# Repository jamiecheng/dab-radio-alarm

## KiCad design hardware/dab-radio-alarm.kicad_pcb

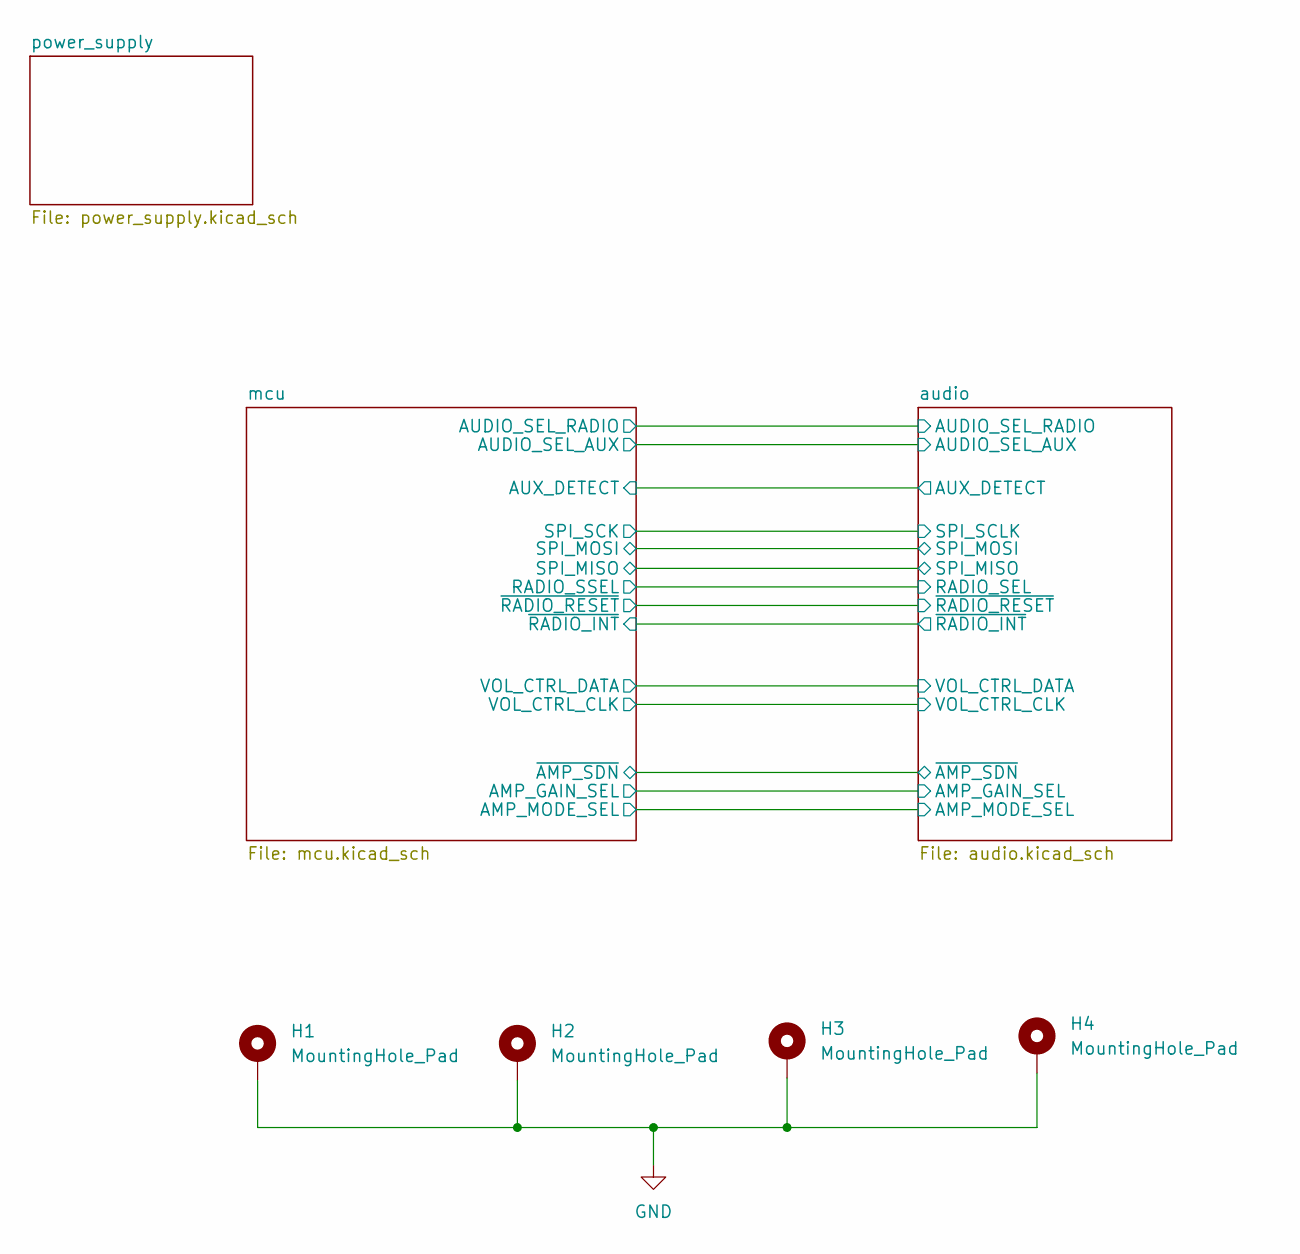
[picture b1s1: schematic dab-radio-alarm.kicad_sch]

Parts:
H1, H2, H3, H4: MountingHole_Pad; MountingHole_3.2mm_M3_Pad_Via

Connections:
GND: H1.1, H2.1, H3.1, H4.1; also elsewhere on the board

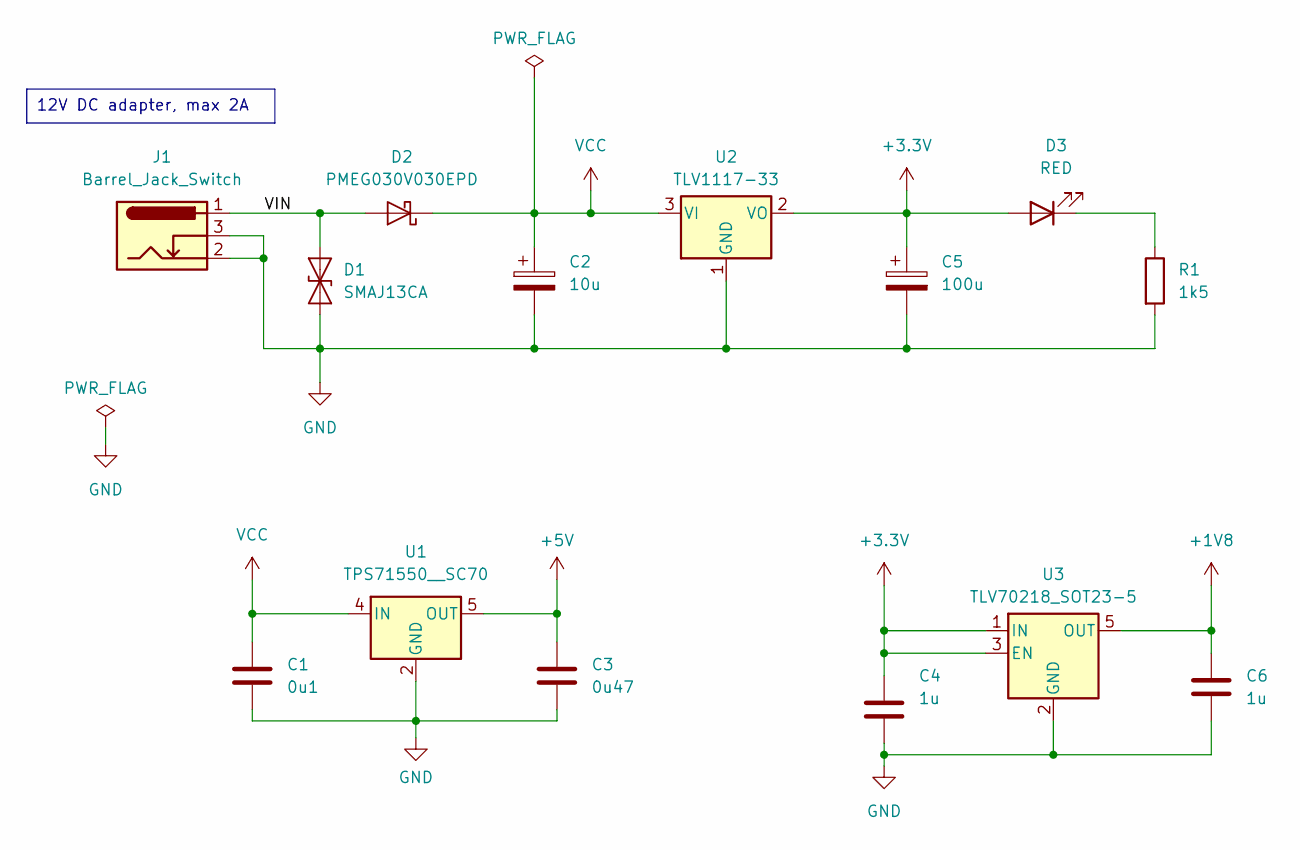
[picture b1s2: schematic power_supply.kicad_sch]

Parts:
C1: 0u1; C_0603_1608Metric
C2: 10u; CP_Elec_6.3x5.4
C3: 0u47; C_0402_1005Metric
C4, C6: 1u; C_0402_1005Metric
C5: 100u; CP_Elec_8x10
D1: SMAJ13CA; D_SMA
D2: PMEG030V030EPD; Nexperia_CFP15_SOT-1289
D3: RED; LED_0603_1608Metric
J1: Barrel_Jack_Switch; BarrelJack_GCT_DCJ200-10-A_Horizontal
R1: 1k5; R_0402_1005Metric
U1: TPS71550__SC70; SOT-353_SC-70-5
U2: TLV1117-33; SOT-223-3_TabPin2
U3: TLV70218_SOT23-5; SOT-23-5

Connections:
+1V8: C6.1, U3.5 (OUT); also elsewhere on the board
+3.3V: C4.1, C5.1, D3.2 (A), U2.2 (VO), U3.1 (IN), U3.3 (EN); also elsewhere on the board
+5V: C3.1, U1.5 (OUT); also elsewhere on the board
/power_supply/VIN: D1.1 (A1), D2.1 (A), D2.2 (A), J1.1
GND: C1.2, C2.2, C3.2, C4.2, C5.2, C6.2, D1.2 (A2), J1.2, J1.3, R1.2, U1.2 (GND), U2.1 (GND), U3.2 (GND); also elsewhere on the board
unnamed: D3.1 (K), R1.1
VCC: C1.1, C2.1, D2.3 (K), U1.4 (IN), U2.3 (VI); also elsewhere on the board

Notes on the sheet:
12V DC adapter, max 2A

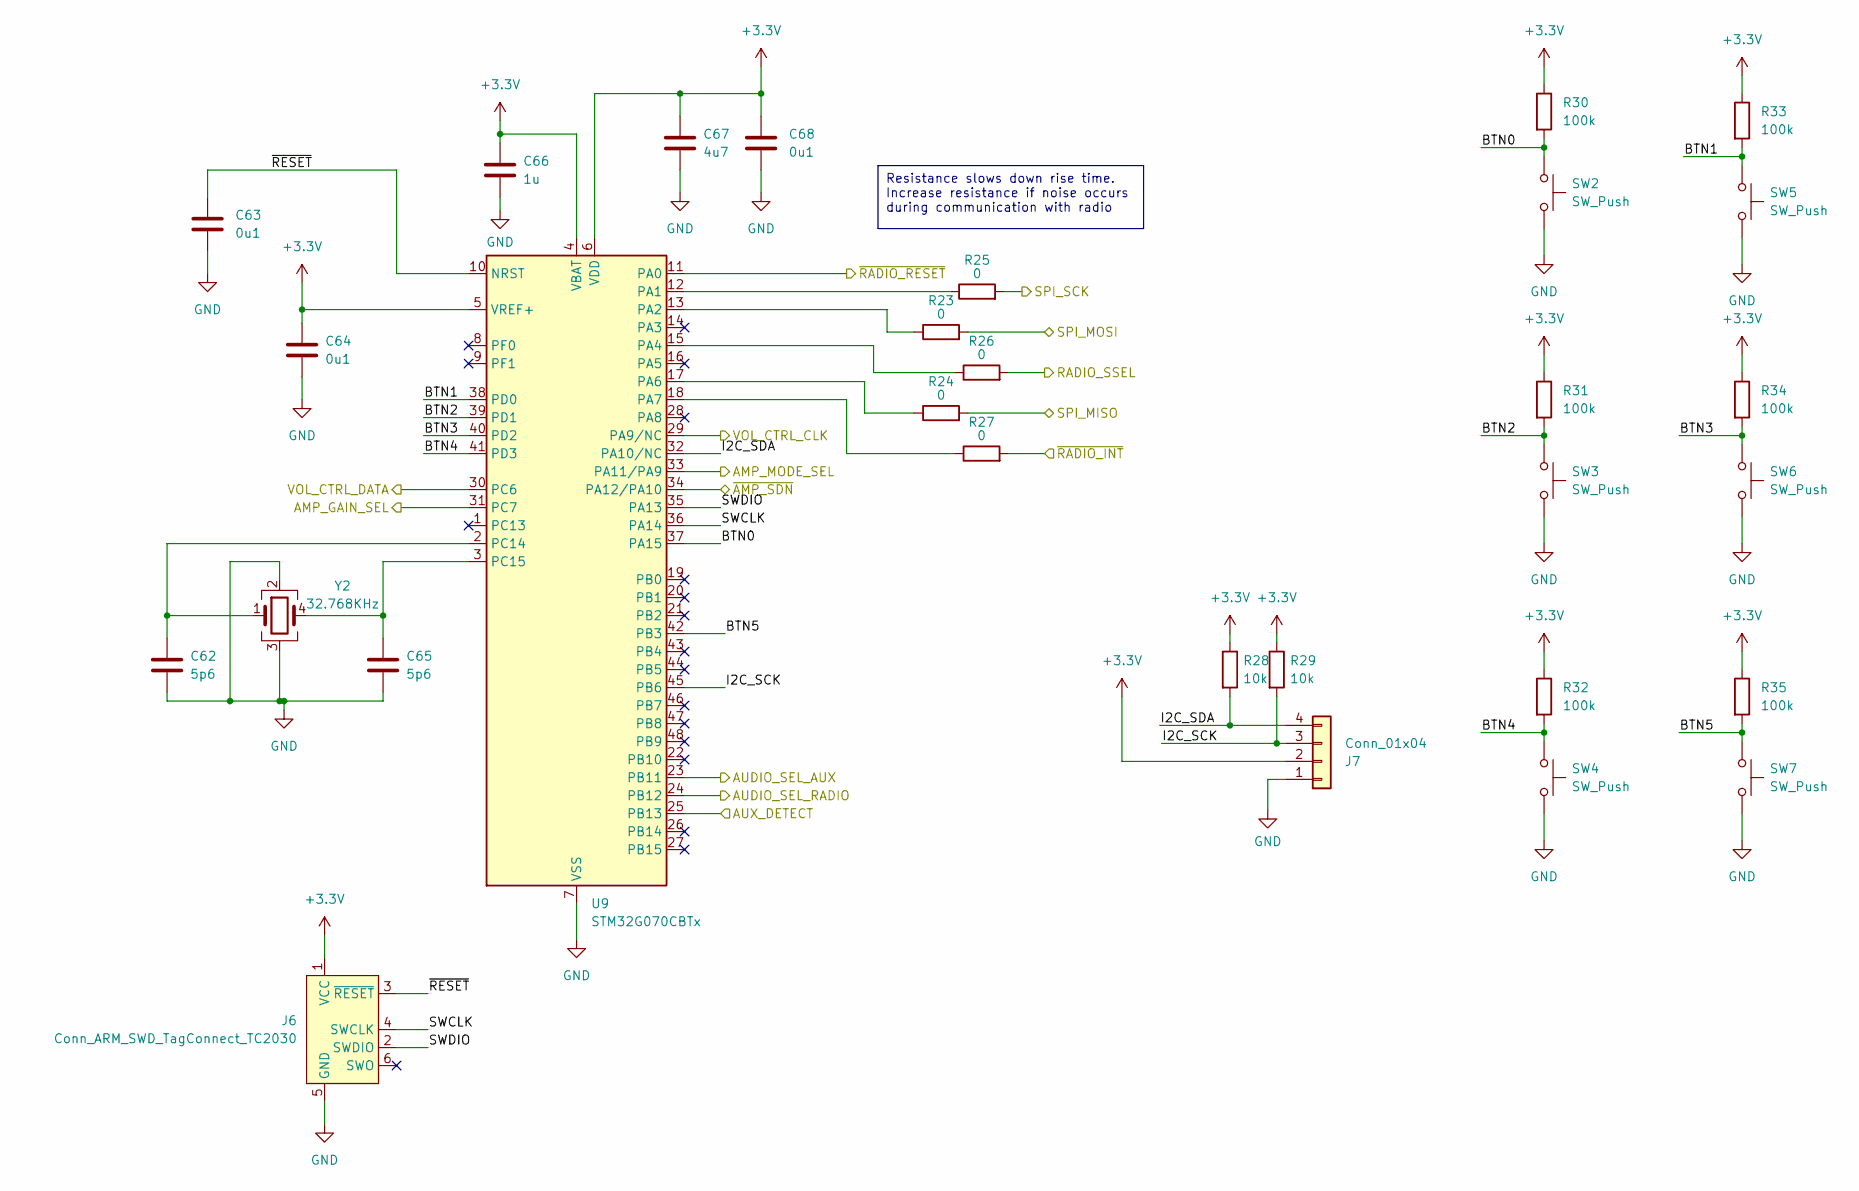
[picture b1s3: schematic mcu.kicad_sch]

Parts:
C62, C65: 5p6; C_0402_1005Metric
C63, C64, C68: 0u1; C_0402_1005Metric
C66: 1u; C_0402_1005Metric
C67: 4u7; C_0603_1608Metric
J6: Conn_ARM_SWD_TagConnect_TC2030; Tag-Connect_TC2030-IDC-FP_2x03_P1.27mm_Vertical
J7: Conn_01x04; PinHeader_1x04_P2.54mm_Vertical
R23, R24, R25, R26, R27: 0; R_0402_1005Metric
R28, R29: 10k; R_0402_1005Metric
R30, R31, R32, R33, R34, R35: 100k; R_0402_1005Metric
SW2, SW3, SW4, SW5, SW6, SW7: SW_Push; SW_PUSH_6mm_H5mm
U9: STM32G070CBTx; LQFP-48_7x7mm_P0.5mm
Y2: 32.768KHz; Crystal_SMD_3225-4Pin_3.2x2.5mm

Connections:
+3.3V: C64.1, C66.1, C67.1, C68.1, J6.1 (VCC), J7.2, R28.1, R29.1, R30.1, R31.1, R32.1, R33.1, R34.1, R35.1, U9.4 (VBAT), U9.5 (VREF+), U9.6 (VDD); also elsewhere on the board
/audio/AMP_GAIN_SEL: U9.31 (PC7); also elsewhere on the board
/audio/AMP_MODE_SEL: U9.33 (PA11/PA9); also elsewhere on the board
/audio/AUDIO_SEL_AUX: U9.23 (PB11); also elsewhere on the board
/audio/AUDIO_SEL_RADIO: U9.24 (PB12); also elsewhere on the board
/audio/AUX_DETECT: U9.25 (PB13); also elsewhere on the board
/audio/RADIO_SEL: R26.2; also elsewhere on the board
/audio/SPI_MISO: R24.2; also elsewhere on the board
/audio/SPI_MOSI: R23.2; also elsewhere on the board
/audio/SPI_SCLK: R25.2; also elsewhere on the board
/audio/VOL_CTRL_CLK: U9.29 (PA9/NC); also elsewhere on the board
/audio/VOL_CTRL_DATA: U9.30 (PC6); also elsewhere on the board
/audio/~AMP_SDN: U9.34 (PA12/PA10); also elsewhere on the board
/audio/~RADIO_INT: R27.2; also elsewhere on the board
/audio/~RADIO_RESET: U9.11 (PA0); also elsewhere on the board
/mcu/BTN0: R30.2, SW2.1, U9.37 (PA15)
/mcu/BTN1: R33.2, SW5.1, U9.38 (PD0)
/mcu/BTN2: R31.2, SW3.1, U9.39 (PD1)
/mcu/BTN3: R34.2, SW6.1, U9.40 (PD2)
/mcu/BTN4: R32.2, SW4.1, U9.41 (PD3)
/mcu/BTN5: R35.2, SW7.1, U9.42 (PB3)
/mcu/I2C_SCK: J7.3, R29.2, U9.45 (PB6)
/mcu/I2C_SDA: J7.4, R28.2, U9.32 (PA10/NC)
/mcu/SWCLK: J6.4 (SWCLK), U9.36 (PA14)
/mcu/SWDIO: J6.2 (SWDIO), U9.35 (PA13)
/mcu/~RESET: C63.1, J6.3 (~RESET), U9.10 (NRST)
GND: C62.2, C63.2, C64.2, C65.2, C66.2, C67.2, C68.2, J6.5 (GND), J7.1, SW2.2, SW3.2, SW4.2, SW5.2, SW6.2, SW7.2, U9.7 (VSS), Y2.2, Y2.3; also elsewhere on the board
unnamed: R25.1, U9.12 (PA1)
unnamed: R23.1, U9.13 (PA2)
unnamed: R26.1, U9.15 (PA4)
unnamed: R24.1, U9.17 (PA6)
unnamed: R27.1, U9.18 (PA7)
unnamed: C62.1, U9.2 (PC14), Y2.1
unnamed: C65.1, U9.3 (PC15), Y2.4

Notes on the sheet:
Resistance slows down rise time. Increase resistance if noise occurs during communication with radio

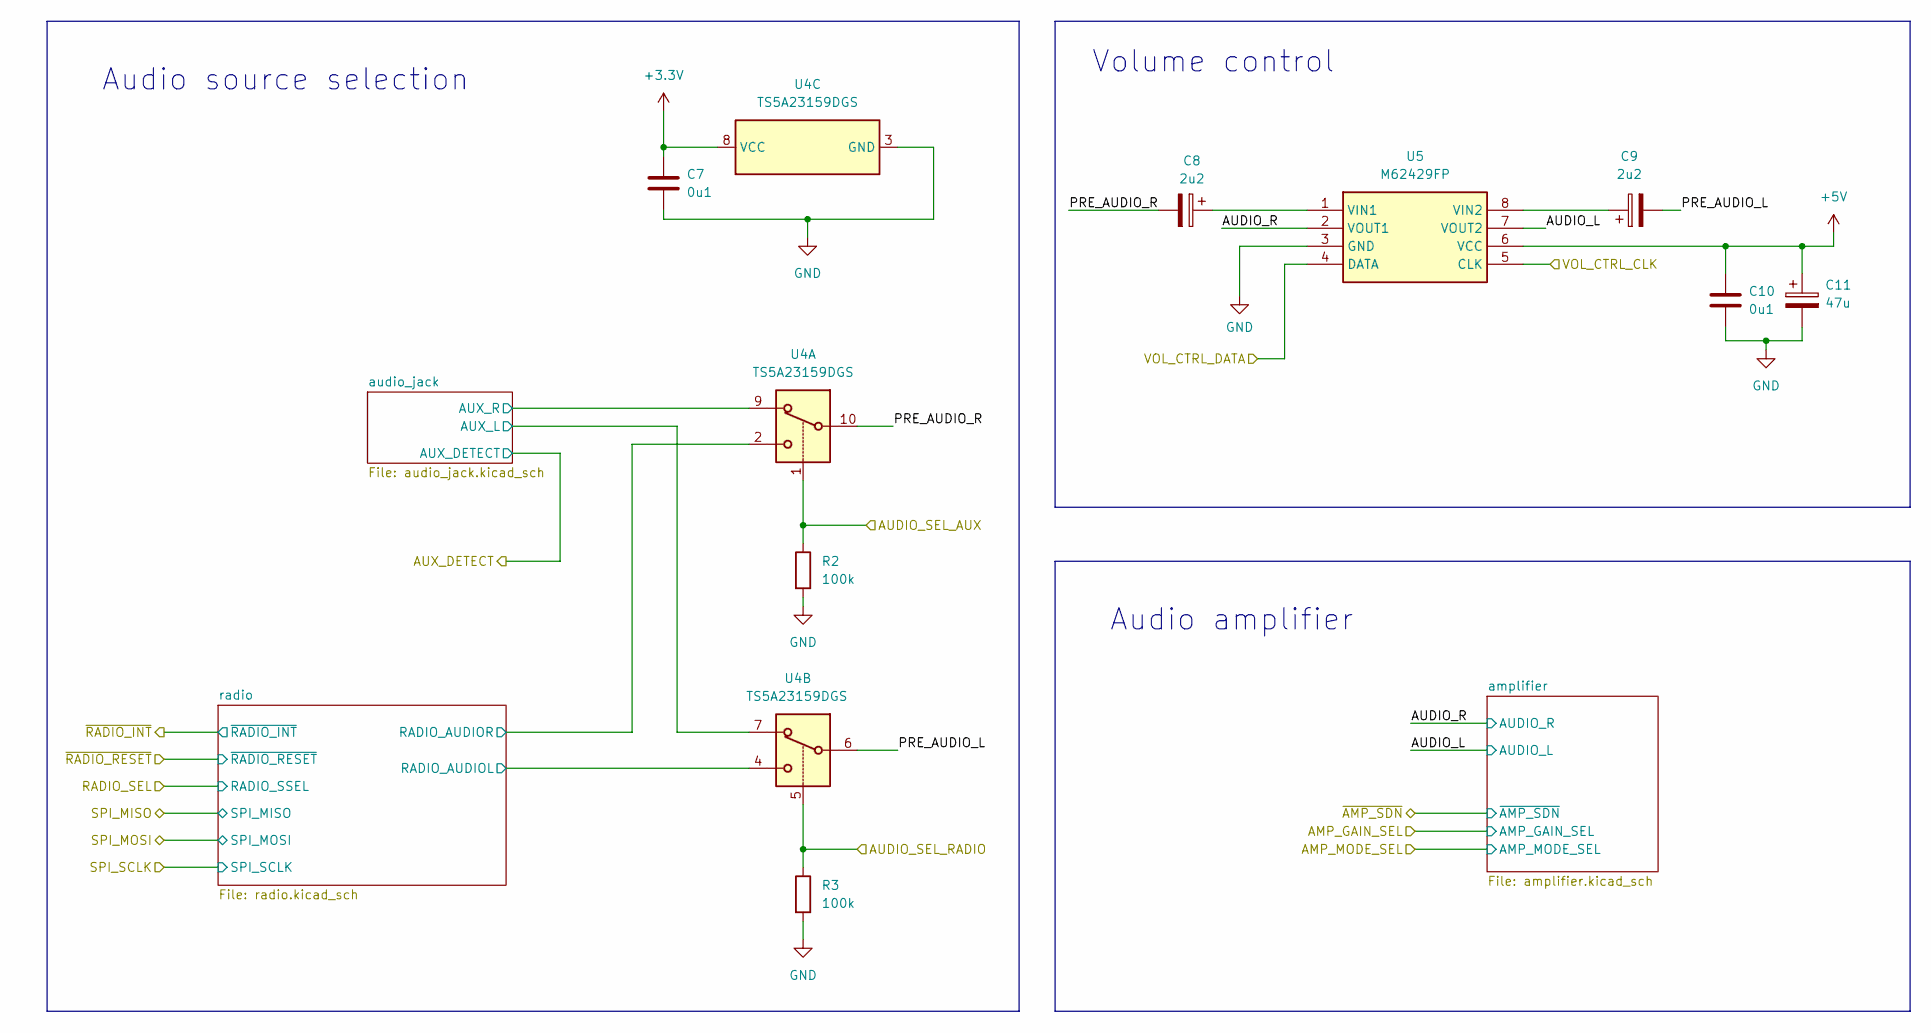
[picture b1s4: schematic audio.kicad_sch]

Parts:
C7, C10: 0u1; C_0402_1005Metric
C8, C9: 2u2; CP_Elec_4x5.4
C11: 47u; CP_Elec_5x5.4
R2, R3: 100k; R_0402_1005Metric
U4: TS5A23159DGS; VSSOP-10_3x3mm_P0.5mm
U5: M62429FP; SOP-8_3.9x4.9mm_P1.27mm; Manufacturer_Part_Number M62429FP

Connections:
+3.3V: C7.1, U4.8 (VCC); also elsewhere on the board
+5V: C10.1, C11.1, U5.6 (VCC); also elsewhere on the board
/audio/AUDIO_L: U5.7 (VOUT2); also elsewhere on the board
/audio/AUDIO_R: U5.2 (VOUT1); also elsewhere on the board
/audio/AUDIO_SEL_AUX: R2.1, U4.1; also elsewhere on the board
/audio/AUDIO_SEL_RADIO: R3.1, U4.5; also elsewhere on the board
/audio/PRE_AUDIO_L: C9.2, U4.6
/audio/PRE_AUDIO_R: C8.2, U4.10
/audio/VOL_CTRL_CLK: U5.5 (CLK); also elsewhere on the board
/audio/VOL_CTRL_DATA: U5.4 (DATA); also elsewhere on the board
/audio/audio_jack/AUX_L: U4.7; also elsewhere on the board
/audio/audio_jack/AUX_R: U4.9; also elsewhere on the board
/audio/radio/RADIO_AUDIOL: U4.4; also elsewhere on the board
/audio/radio/RADIO_AUDIOR: U4.2; also elsewhere on the board
GND: C7.2, C10.2, C11.2, R2.2, R3.2, U4.3 (GND), U5.3 (GND); also elsewhere on the board
unnamed: C8.1, U5.1 (VIN1)
unnamed: C9.1, U5.8 (VIN2)

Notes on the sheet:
Volume control
Audio amplifier
Audio source selection

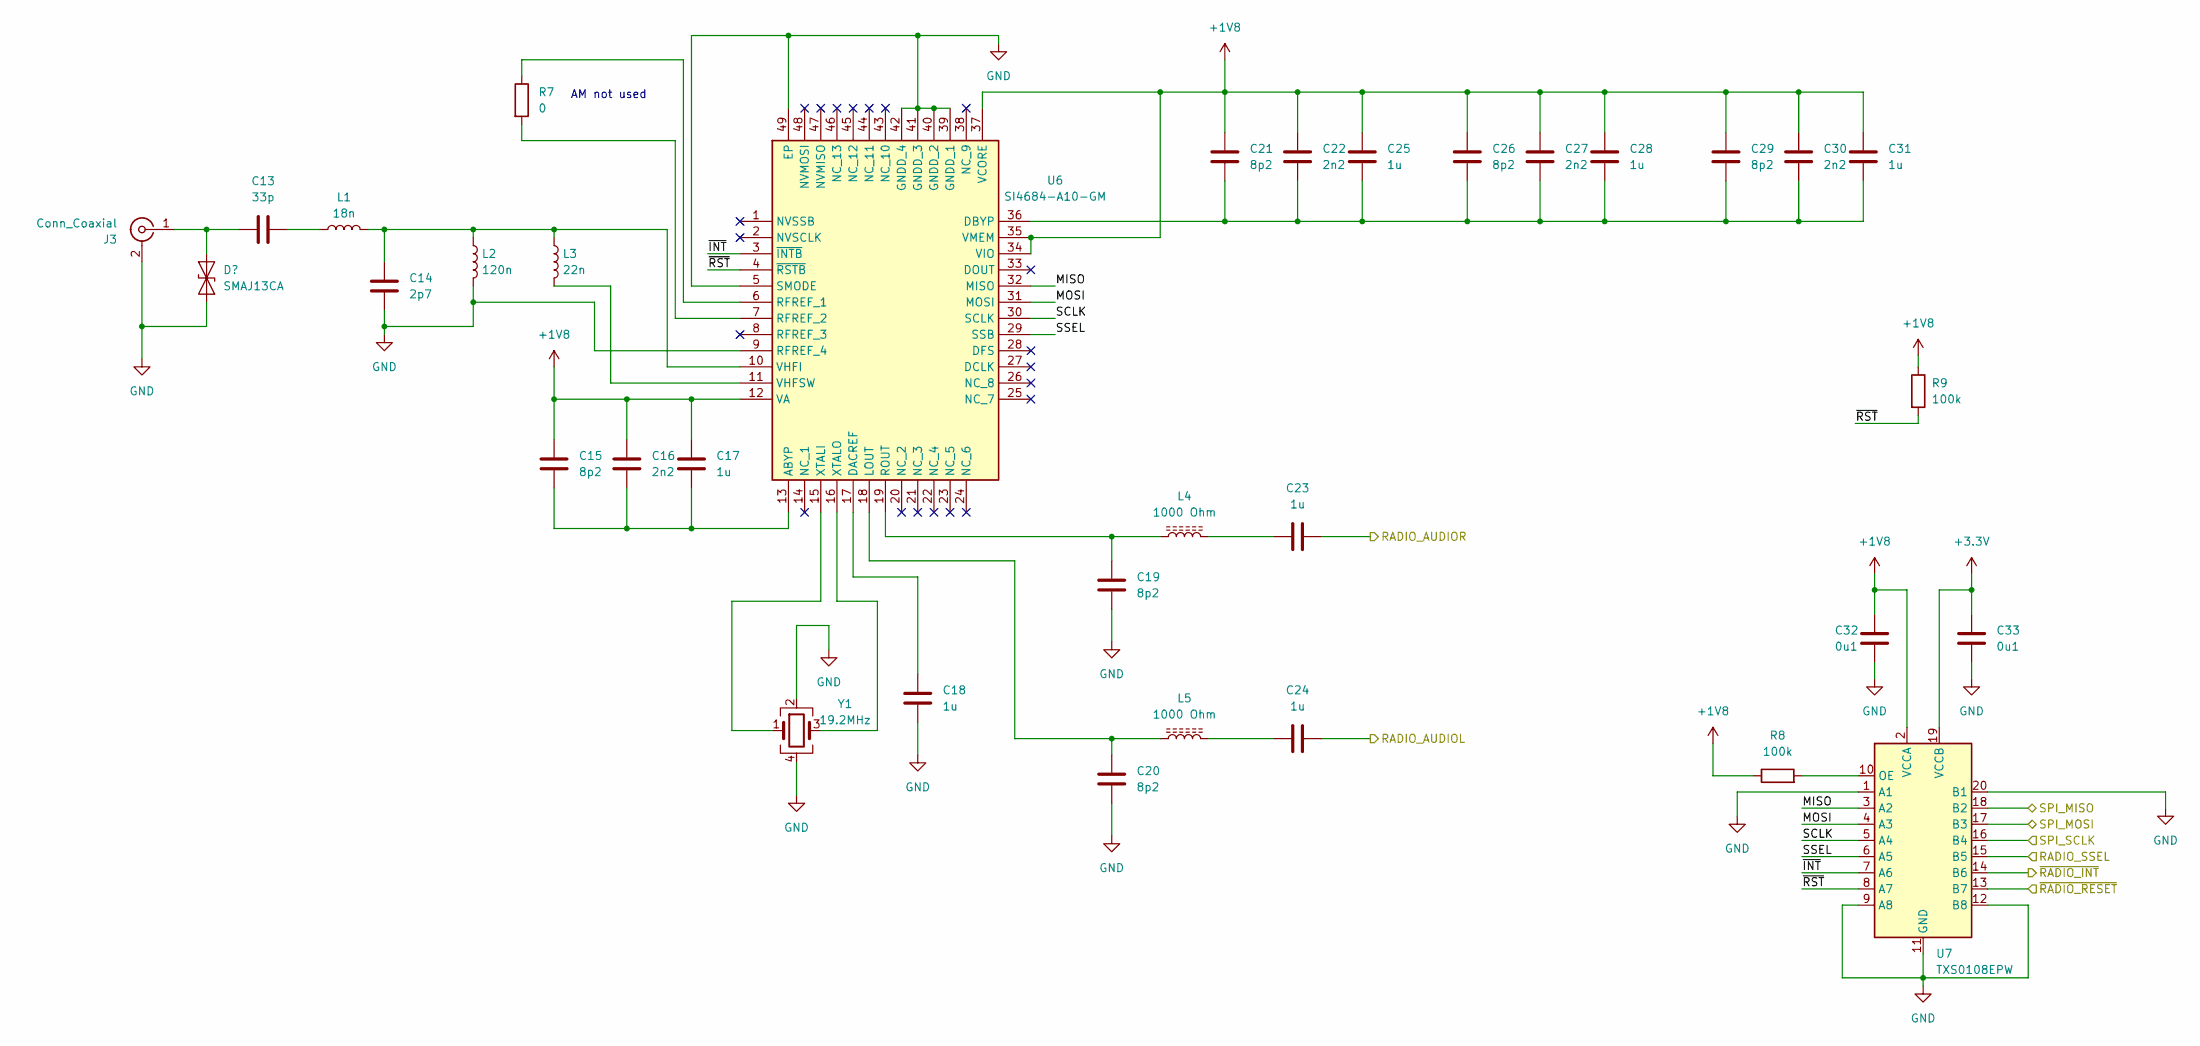
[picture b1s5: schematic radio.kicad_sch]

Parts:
C13: 33p; C_0402_1005Metric
C14: 2p7; C_0402_1005Metric
C15, C19, C20, C21, C26, C29: 8p2; C_0402_1005Metric
C16, C22, C27, C30: 2n2; C_0402_1005Metric
C17, C18, C23, C24, C25, C28, C31: 1u; C_0402_1005Metric
C32, C33: 0u1; C_0402_1005Metric
D7: SMAJ13CA; D_SMA
J3: Conn_Coaxial; SMA_Molex_73251-1153_EdgeMount_Horizontal
L1: 18n; L_0402_1005Metric
L2: 120n; L_0402_1005Metric
L3: 22n; L_0402_1005Metric
L4, L5: 1000 Ohm; L_0402_1005Metric
R7: 0; R_0402_1005Metric
R8, R9: 100k; R_0402_1005Metric
U6: SI4684-A10-GM; NXP_LQFN-48-1EP_7x7mm_P0.5mm_EP3.5x3.5mm_16xMask0.45x0.45; Manufacturer_Part_Number SI4684-A10-GM; Mouser Part Number 634-SI4684-A10-GM
U7: TXS0108EPW; TSSOP-20_4.4x6.5mm_P0.65mm
Y1: 19.2MHz; Crystal_SMD_EuroQuartz_MT-4Pin_3.2x2.5mm

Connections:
+1V8: C15.1, C16.1, C17.1, C21.1, C22.1, C25.1, C26.1, C27.1, C28.1, C29.1, C30.1, C31.1, C32.1, R8.1, R9.1, U6.12 (VA), U6.34 (VIO), U6.35 (VMEM), U6.37 (VCORE), U7.2 (VCCA); also elsewhere on the board
+3.3V: C33.1, U7.19 (VCCB); also elsewhere on the board
/audio/RADIO_SEL: U7.15 (B5); also elsewhere on the board
/audio/SPI_MISO: U7.18 (B2); also elsewhere on the board
/audio/SPI_MOSI: U7.17 (B3); also elsewhere on the board
/audio/SPI_SCLK: U7.16 (B4); also elsewhere on the board
/audio/radio/MISO: U6.32 (MISO), U7.3 (A2)
/audio/radio/MOSI: U6.31 (MOSI), U7.4 (A3)
/audio/radio/RADIO_AUDIOL: C24.2; also elsewhere on the board
/audio/radio/RADIO_AUDIOR: C23.2; also elsewhere on the board
/audio/radio/SCLK: U6.30 (SCLK), U7.5 (A4)
/audio/radio/SSEL: U6.29 (SSB), U7.6 (A5)
/audio/radio/~INT: U6.3 (~INTB), U7.7 (A6)
/audio/radio/~RST: R9.2, U6.4 (~RSTB), U7.8 (A7)
/audio/~RADIO_INT: U7.14 (B6); also elsewhere on the board
/audio/~RADIO_RESET: U7.13 (B7); also elsewhere on the board
GND: C14.2, C18.2, C19.2, C20.2, C32.2, C33.2, D7.2 (A2), J3.2 (Ext), L2.2, U6.5 (SMODE), U6.9 (RFREF_4), U6.39 (GNDD_1), U6.40 (GNDD_2), U6.41 (GNDD_3), U6.42 (GNDD_4), U6.49 (EP), U7.1 (A1), U7.9 (A8), U7.11 (GND), U7.12 (B8), U7.20 (B1), Y1.2, Y1.4; also elsewhere on the board
unnamed: C13.2, L1.1
unnamed: C23.1, L4.2
unnamed: C24.1, L5.2
unnamed: C13.1, D7.1 (A1), J3.1 (In)
unnamed: C15.2, C16.2, C17.2, U6.13 (ABYP)
unnamed: C18.1, U6.17 (DACREF)
unnamed: C21.2, C22.2, C25.2, C26.2, C27.2, C28.2, C29.2, C30.2, C31.2, U6.36 (DBYP)
unnamed: C20.1, L5.1, U6.18 (LOUT)
unnamed: R7.1, U6.6 (RFREF_1)
unnamed: R7.2, U6.7 (RFREF_2)
unnamed: C19.1, L4.1, U6.19 (ROUT)
unnamed: C14.1, L1.2, L2.1, L3.1, U6.10 (VHFI)
unnamed: L3.2, U6.11 (VHFSW)
unnamed: U6.15 (XTALI), Y1.1
unnamed: U6.16 (XTALO), Y1.3
unnamed: R8.2, U7.10 (OE)

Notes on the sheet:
AM not used

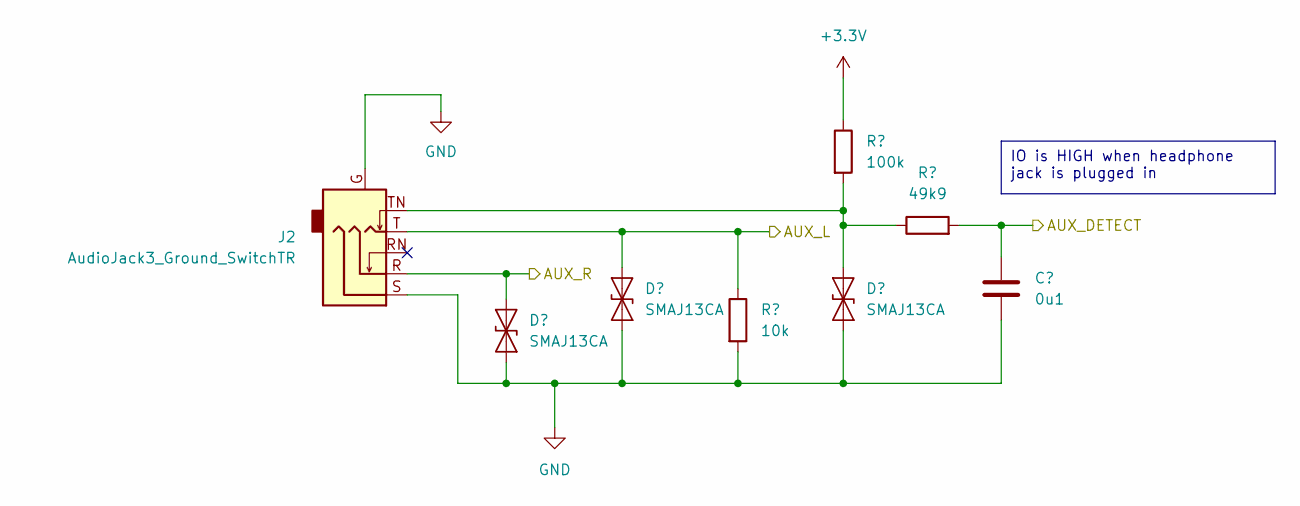
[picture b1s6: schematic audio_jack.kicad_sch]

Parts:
C12: 0u1; C_0402_1005Metric
D4, D5, D6: SMAJ13CA; D_SMA
J2: AudioJack3_Ground_SwitchTR; Jack_3.5mm_PJ31060-I_Horizontal_1
R4: 10k; R_0402_1005Metric
R5: 100k; R_0402_1005Metric
R6: 49k9; R_0402_1005Metric

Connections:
+3.3V: R5.1; also elsewhere on the board
/audio/AUX_DETECT: C12.1, R6.2; also elsewhere on the board
/audio/audio_jack/AUX_L: D5.1 (A1), J2.T, R4.1; also elsewhere on the board
/audio/audio_jack/AUX_R: D4.1 (A1), J2.R; also elsewhere on the board
GND: C12.2, D4.2 (A2), D5.2 (A2), D6.2 (A2), J2.G, J2.S, R4.2; also elsewhere on the board
unnamed: D6.1 (A1), J2.TN, R5.2, R6.1

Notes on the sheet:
IO is HIGH when headphone jack is plugged in

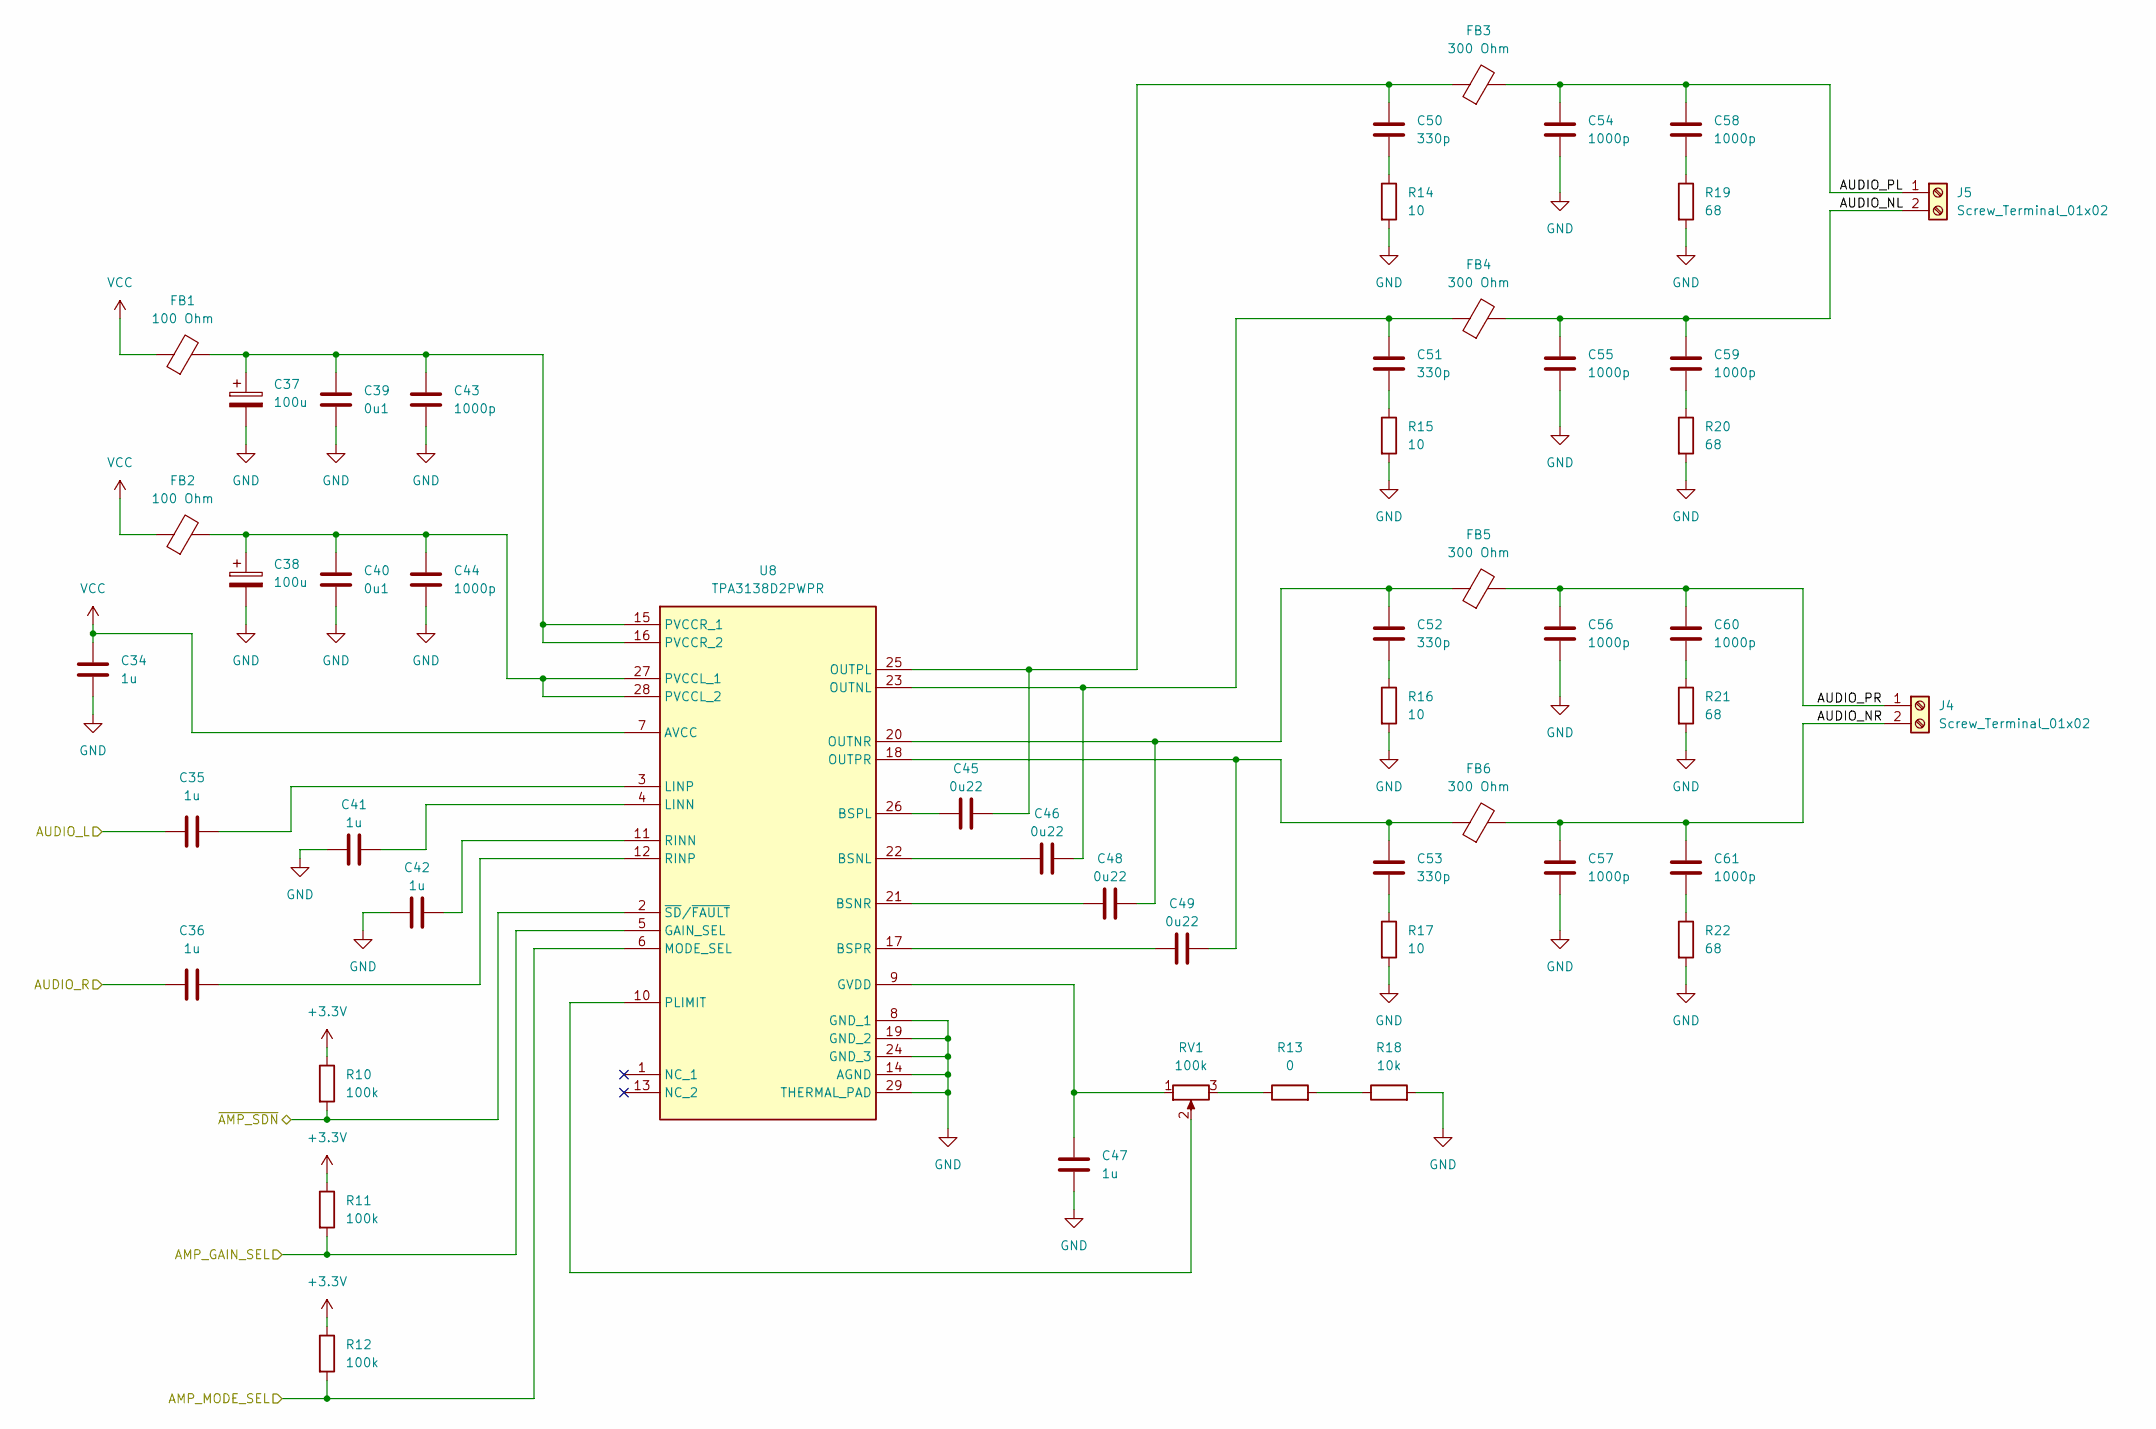
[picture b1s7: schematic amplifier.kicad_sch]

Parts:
C34, C35, C36, C41, C42, C47: 1u; C_0603_1608Metric
C37, C38: 100u; CP_Elec_8x10
C39, C40: 0u1; C_0603_1608Metric
C43, C44, C54, C55, C56, C57, C58, C59, C60, C61: 1000p; C_0603_1608Metric
C45, C46, C48, C49: 0u22; C_0603_1608Metric
C50, C51, C52, C53: 330p; C_0603_1608Metric
FB1, FB2: 100 Ohm; L_0805_2012Metric
FB3, FB4, FB5, FB6: 300 Ohm; L_0805_2012Metric
J4, J5: Screw_Terminal_01x02; TerminalBlock_MetzConnect_Type011_RT05502HBWC_1x02_P5.00mm_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
R10, R11, R12: 100k; R_0402_1005Metric
R13: 0; R_0402_1005Metric
R14, R15, R16, R17: 10; R_0603_1608Metric
R18: 10k; R_0402_1005Metric
R19, R20, R21, R22: 68; R_0603_1608Metric
RV1: 100k; Potentiometer_Bourns_3314G_Vertical
U8: TPA3138D2PWPR; HTSSOP-28-1EP_4.4x9.7mm_P0.65mm_EP2.85x5.4mm_ThermalVias; Manufacturer_Part_Number TPA3138D2PWPR; Mouser Part Number 595-TPA3138D2PWPR

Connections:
+3.3V: R10.1, R11.1, R12.1; also elsewhere on the board
/audio/AMP_GAIN_SEL: R11.2, U8.5 (GAIN_SEL); also elsewhere on the board
/audio/AMP_MODE_SEL: R12.2, U8.6 (MODE_SEL); also elsewhere on the board
/audio/AUDIO_L: C35.1; also elsewhere on the board
/audio/AUDIO_R: C36.1; also elsewhere on the board
/audio/amplifier/AUDIO_NL: C55.1, C59.1, FB4.2, J5.2
/audio/amplifier/AUDIO_NR: C57.1, C61.1, FB6.2, J4.2
/audio/amplifier/AUDIO_PL: C54.1, C58.1, FB3.2, J5.1
/audio/amplifier/AUDIO_PR: C56.1, C60.1, FB5.2, J4.1
/audio/~AMP_SDN: R10.2, U8.2 (~SD/~FAULT); also elsewhere on the board
GND: C34.2, C37.2, C38.2, C39.2, C40.2, C41.1, C42.1, C43.2, C44.2, C47.2, C54.2, C55.2, C56.2, C57.2, R14.2, R15.2, R16.2, R17.2, R18.2, R19.2, R20.2, R21.2, R22.2, U8.8 (GND_1), U8.14 (AGND), U8.19 (GND_2), U8.24 (GND_3), U8.29 (THERMAL_PAD); also elsewhere on the board
unnamed: C50.2, R14.1
unnamed: C51.2, R15.1
unnamed: C52.2, R16.1
unnamed: C53.2, R17.1
unnamed: C58.2, R19.1
unnamed: C59.2, R20.1
unnamed: C60.2, R21.1
unnamed: C61.2, R22.1
unnamed: R13.1, RV1.3
unnamed: R13.2, R18.1
unnamed: C46.1, U8.22 (BSNL)
unnamed: C48.1, U8.21 (BSNR)
unnamed: C45.1, U8.26 (BSPL)
unnamed: C49.1, U8.17 (BSPR)
unnamed: C47.1, RV1.1, U8.9 (GVDD)
unnamed: C41.2, U8.4 (LINN)
unnamed: C35.2, U8.3 (LINP)
unnamed: C46.2, C51.1, FB4.1, U8.23 (OUTNL)
unnamed: C48.2, C52.1, FB5.1, U8.20 (OUTNR)
unnamed: C45.2, C50.1, FB3.1, U8.25 (OUTPL)
unnamed: C49.2, C53.1, FB6.1, U8.18 (OUTPR)
unnamed: RV1.2, U8.10 (PLIMIT)
unnamed: C38.1, C40.1, C44.1, FB2.2, U8.27 (PVCCL_1), U8.28 (PVCCL_2)
unnamed: C37.1, C39.1, C43.1, FB1.2, U8.15 (PVCCR_1), U8.16 (PVCCR_2)
unnamed: C42.2, U8.11 (RINN)
unnamed: C36.2, U8.12 (RINP)
VCC: C34.1, FB1.1, FB2.1, U8.7 (AVCC); also elsewhere on the board

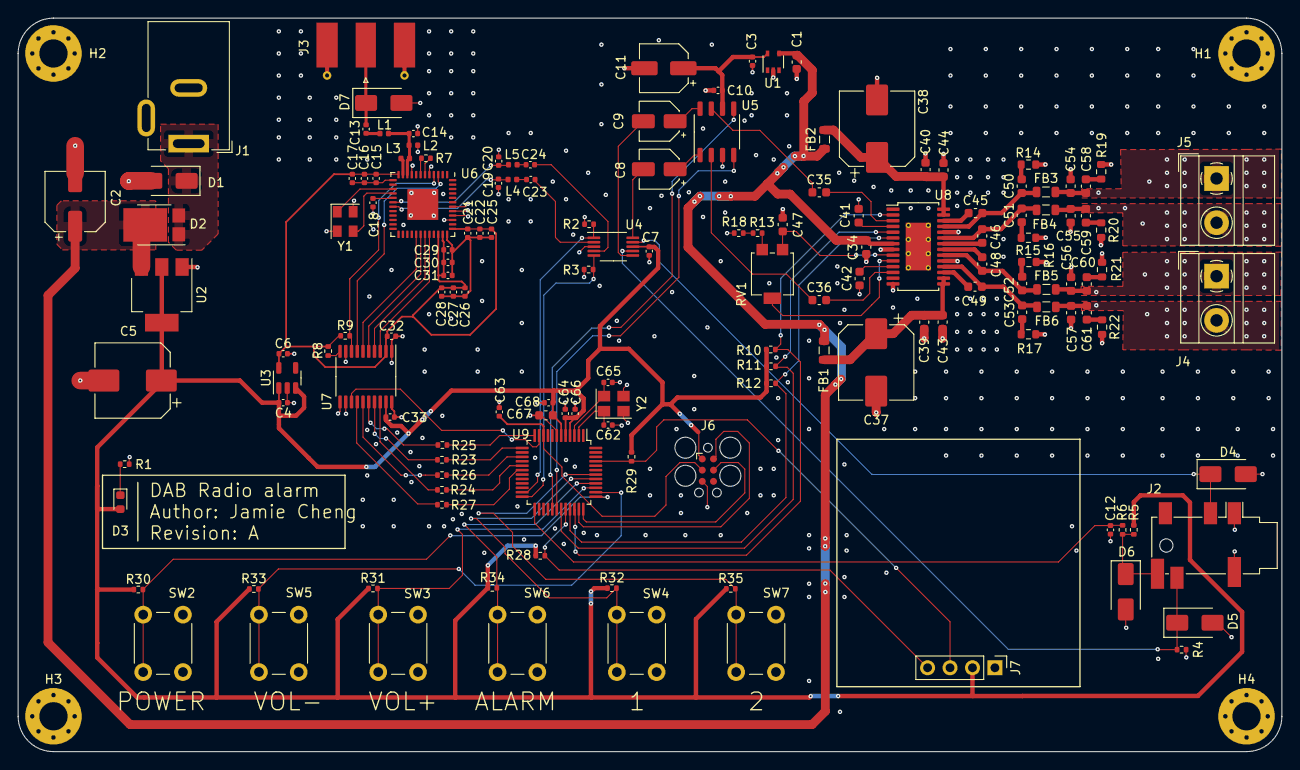
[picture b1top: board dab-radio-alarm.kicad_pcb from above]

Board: 4 copper layers, 143.0 x 83.0 mm, 150 parts (0 on the bottom side), 102 nets.

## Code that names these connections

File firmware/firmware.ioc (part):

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Mcu.Name=STM32G070CBTx
Mcu.Package=LQFP48
Mcu.UserName=STM32G070CBTx
PA0.GPIOParameters=GPIO_Label
PA0.GPIO_Label=RADIO_RESET
PA0.Signal=GPIO_Output
PA1.Mode=Full_Duplex_Master
PA1.Signal=SPI1_SCK
PA10.Mode=I2C
PA10.Signal=I2C1_SDA
PA11\ [PA9].GPIOParameters=GPIO_Label
PA11\ [PA9].GPIO_Label=AMP_MODE_SEL
PA11\ [PA9].Signal=GPIO_Output
PA12\ [PA10].GPIOParameters=GPIO_Label
PA12\ [PA10].GPIO_Label=AMP_SDN
PA12\ [PA10].Signal=GPIO_Output
PA13.Mode=Serial_Wire
PA13.Signal=SYS_SWDIO
PA14-BOOT0.Mode=Serial_Wire
PA14-BOOT0.Signal=SYS_SWCLK
PA15.GPIOParameters=GPIO_Label
PA15.GPIO_Label=BT0
PA15.Signal=GPIO_Input
PA2.Mode=Full_Duplex_Master
PA2.Signal=SPI1_MOSI
PA4.Mode=NSS_Signal_Hard_Output
PA4.Signal=SPI1_NSS
PA6.Mode=Full_Duplex_Master
PA6.Signal=SPI1_MISO
PA7.GPIOParameters=GPIO_Label
PA7.GPIO_Label=RADIO_INT
PA7.Signal=GPIO_Input
PA9.GPIOParameters=GPIO_Label
PA9.GPIO_Label=VOL_CTRL_CLK
PA9.Signal=GPIO_Output
PB11.GPIOParameters=GPIO_Label
PB11.GPIO_Label=AUDIO_SEL_AUX
PB11.Signal=GPIO_Output
PB12.GPIOParameters=GPIO_Label
PB12.GPIO_Label=AUDIO_SEL_RADIO
PB12.Signal=GPIO_Output
PB13.GPIOParameters=GPIO_Label
PB13.GPIO_Label=AUX_DETECT
PB13.Signal=GPIO_Input
PB3.GPIOParameters=GPIO_Label
PB3.GPIO_Label=BT5
PB3.Signal=GPIO_Input
PB6.Mode=I2C
PB6.Signal=I2C1_SCL
PC14-OSC32_IN\ (PC14).Mode=LSE-External-Oscillator
PC14-OSC32_IN\ (PC14).Signal=RCC_OSC32_IN
PC15-OSC32_OUT\ (PC15).Mode=LSE-External-Oscillator
PC15-OSC32_OUT\ (PC15).Signal=RCC_OSC32_OUT
PC6.GPIOParameters=GPIO_Label
PC6.GPIO_Label=VOL_CTRL_DATA
PC6.Signal=GPIO_Output
PC7.GPIOParameters=GPIO_Label
PC7.GPIO_Label=AMP_GAIN_SEL
PC7.Signal=GPIO_Output
PD0.GPIOParameters=GPIO_Label
PD0.GPIO_Label=BT1
PD0.Signal=GPIO_Input
PD1.GPIOParameters=GPIO_Label
PD1.GPIO_Label=BT2
PD1.Signal=GPIO_Input
PD2.GPIOParameters=GPIO_Label
PD2.GPIO_Label=BT3
PD2.Signal=GPIO_Input
PD3.GPIOParameters=GPIO_Label
PD3.GPIO_Label=BT4
PD3.Signal=GPIO_Input
RCC.HSE_VALUE=8000000
RCC.SYSCLKFreq_VALUE=64000000
RCC.SYSCLKSource=RCC_SYSCLKSOURCE_PLLCLK
board=custom

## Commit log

2023-07-09 files upload
